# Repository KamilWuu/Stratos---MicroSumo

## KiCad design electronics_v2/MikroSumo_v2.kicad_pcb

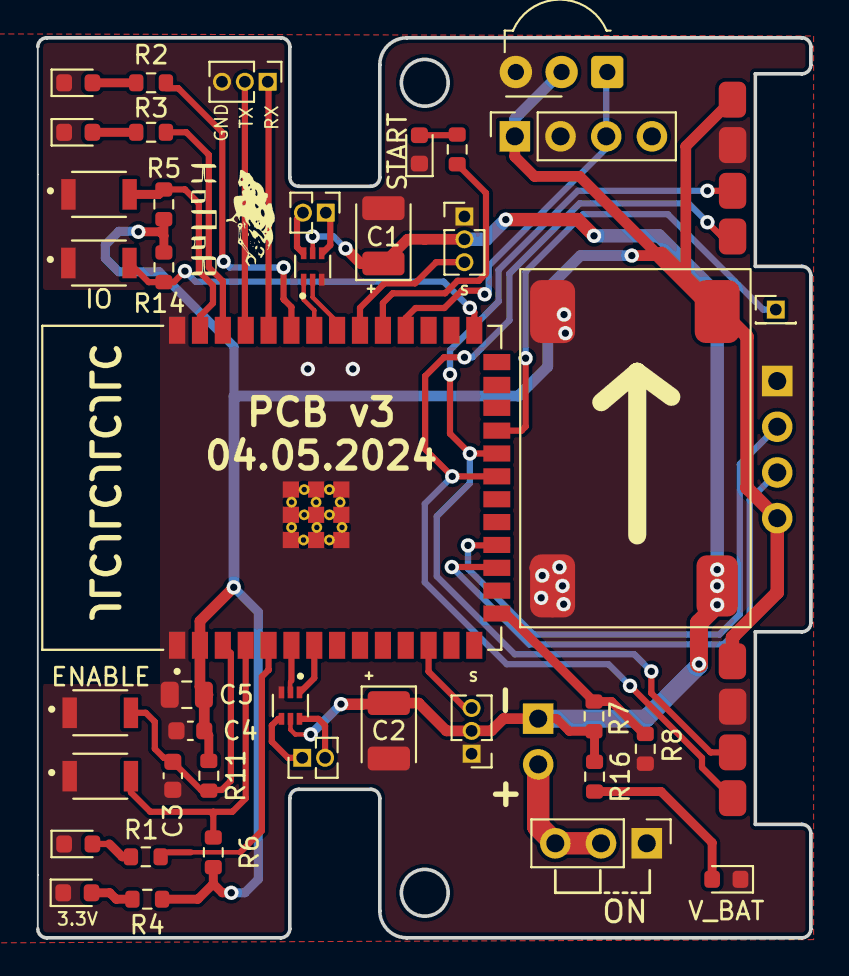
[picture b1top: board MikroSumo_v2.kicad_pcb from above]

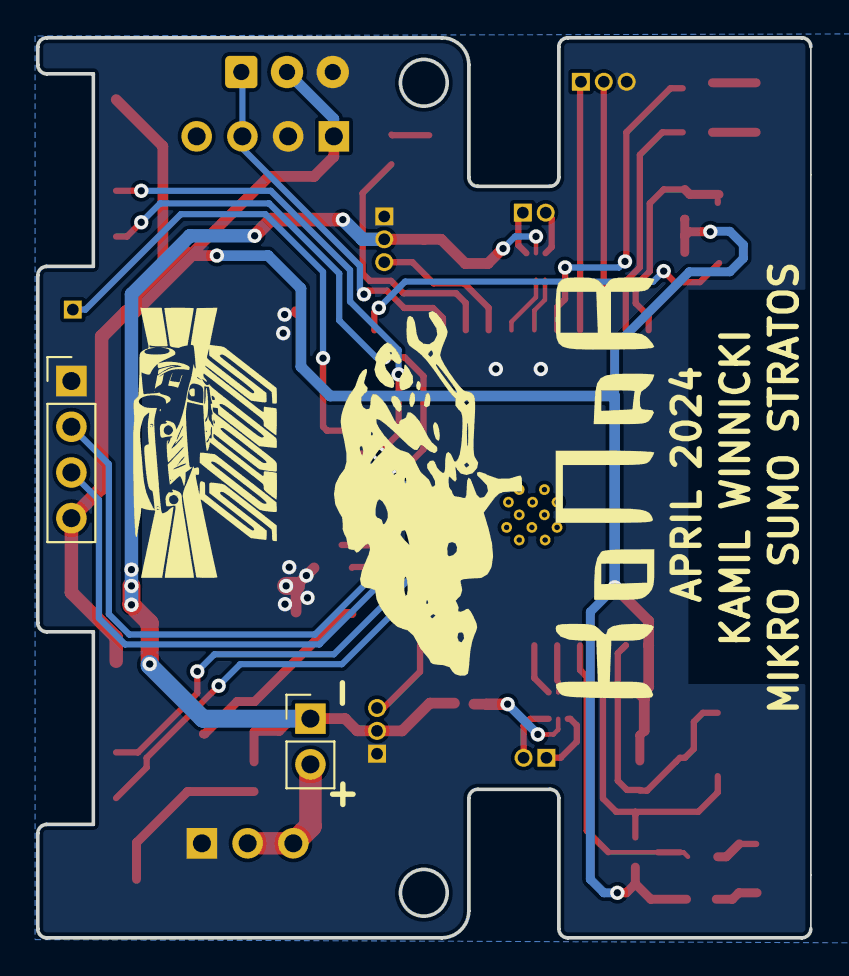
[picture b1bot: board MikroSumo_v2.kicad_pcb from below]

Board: 2 copper layers, 42.9 x 50.0 mm, 44 parts (2 on the bottom side), 37 nets.

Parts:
3.3V: LED; LED_0603_1608Metric
C1, C2: C_Polarized; CP_EIA-3528-21_Kemet-B
C3, C4: 0.1uF; C_0603_1608Metric
C5: 22uF; C_0805_2012Metric
ENABLE: B3U-1000P; SW_B3U-1000P
IO: B3U-1000P; SW_B3U-1000P
J1: Conn_01x04_Female; PinHeader_1x04_P2.54mm_Vertical
J3, J4: Conn_01x02_Male; PinHeader_1x02_P1.27mm_Vertical
J5: Conn_01x01_Male; PinHeader_1x01_P1.27mm_Vertical
J6: Conn_01x03_Male; PinHeader_1x03_P1.27mm_Vertical
J8: Conn_01x04_Female; PinSocket_1x04_P2.54mm_Vertical
J9: Conn_01x03_Pin; PinHeader_1x03_P2.54mm_Vertical
LED1, LED2, LED3: LED; LED_0603_1608Metric
R1, R2, R3, R4, R15: 1K; R_0603_1608Metric
R5, R6, R7, R8, R11, R14: 10K; R_0603_1608Metric
R16: 2K; R_0603_1608Metric
S1, S2: B3U-1000P; SW_B3U-1000P
START: LED; LED_0603_1608Metric
SV1, SV2: Conn_01x03_Male; PinHeader_1x03_P1.27mm_Vertical
U1: MH-MINI-360
U2, U3: DRV8210DRLR; SOT50P160X60-6N
U6, U7: TOFVL53L0X
U8: ESP32-S3-WROOM-1-N8R8; XCVR_ESP32S3WROOM1N8R8
U9: TSOP323xx; Vishay_MOLD-3Pin
V_BAT: LED; LED_0603_1608Metric
batt1: Conn_01x02_Male; PinHeader_1x02_P2.54mm_Vertical

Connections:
+3.3V: C4.2, C5.2, J1.4, J8.1, R4.1, R5.1, R6.1, R11.2, R14.2, U1.4 (OUT+), U6.1 (VIN), U7.1 (VIN), U8.2 (3V3), U9.2 (Vs)
B1: R6.2, S2.2, U8.4 (IO4)
B2: R5.2, S1.2, U8.39 (IO1)
EN: C3.1, ENABLE.2, R11.1, U8.3 (EN)
GND: 3.3V.1 (K), C1.2, C2.2, C3.2, C4.1, C5.1, ENABLE.1, IO.1, J1.1, J6.3, J8.2, J9.1, LED1.1 (K), LED2.1 (K), LED3.1 (K), R8.1, S1.1, S2.1, START.1 (K), SV1.1, SV2.1, U1.1 (IN-), U1.3 (OUT-), U2.3 (GND), U3.3 (GND), U6.2 (GND), U7.2 (GND), U8.1 (GND), U8.40 (GND), U8.41_1 (GND), U8.41_2 (GND), U8.41_3 (GND), U8.41_4 (GND), U8.41_5 (GND), U8.41_6 (GND), U8.41_7 (GND), U8.41_8 (GND), U8.41_9 (GND), U9.3 (GND), V_BAT.1 (K)
IN_1: J1.3, U8.17 (IO9)
IN_2: J1.2, U8.18 (IO10)
IO0: IO.2, R14.1, U8.27 (IO0)
LED1: R1.1, U8.5 (IO5)
LED2: R3.1, U8.38 (IO2)
LED3: R2.1, U8.35 (IO42)
MIN1_1: U2.1 (IN1), U8.7 (IO7)
MIN1_2: U3.1 (IN1), U8.34 (IO41)
MIN2_1: U2.2 (IN2), U8.6 (IO6)
MIN2_2: U3.2 (IN2), U8.33 (IO40)
unnamed: 3.3V.2 (A), R4.2
unnamed: J3.1, U2.4 (OUT2)
unnamed: J3.2, U2.6 (OUT1)
unnamed: J4.1, U3.4 (OUT2)
unnamed: J4.2, U3.6 (OUT1)
unnamed: J9.2, J9.3, batt1.2
unnamed: LED1.2 (A), R1.2
unnamed: LED2.2 (A), R2.2
unnamed: LED3.2 (A), R3.2
unnamed: R15.2, START.2 (A)
unnamed: R16.2, V_BAT.2 (A)
RX: J6.1, U8.36 (RXD0)
SCL: U6.3 (SCL), U7.3 (SCL), U8.22 (IO14)
SDA: U6.4 (SDA), U7.4 (SDA), U8.21 (IO13)
SERVO1: SV1.3, U8.12 (IO8)
SERVO2: SV2.3, U8.32 (IO39)
STARTER: J8.3, U8.30 (IO37), U9.1 (OUT)
STARTER_LED: R15.1, U8.31 (IO38)
TX: J6.2, U8.37 (TXD0)
VCC: C1.1, C2.1, R7.2, R16.1, SV1.2, SV2.2, U1.2 (IN+), U2.5 (VM), U3.5 (VM), batt1.1
V_BAT: R7.1, R8.2, U8.15 (IO3)
XSHUT: J5.1, U8.23 (IO21)

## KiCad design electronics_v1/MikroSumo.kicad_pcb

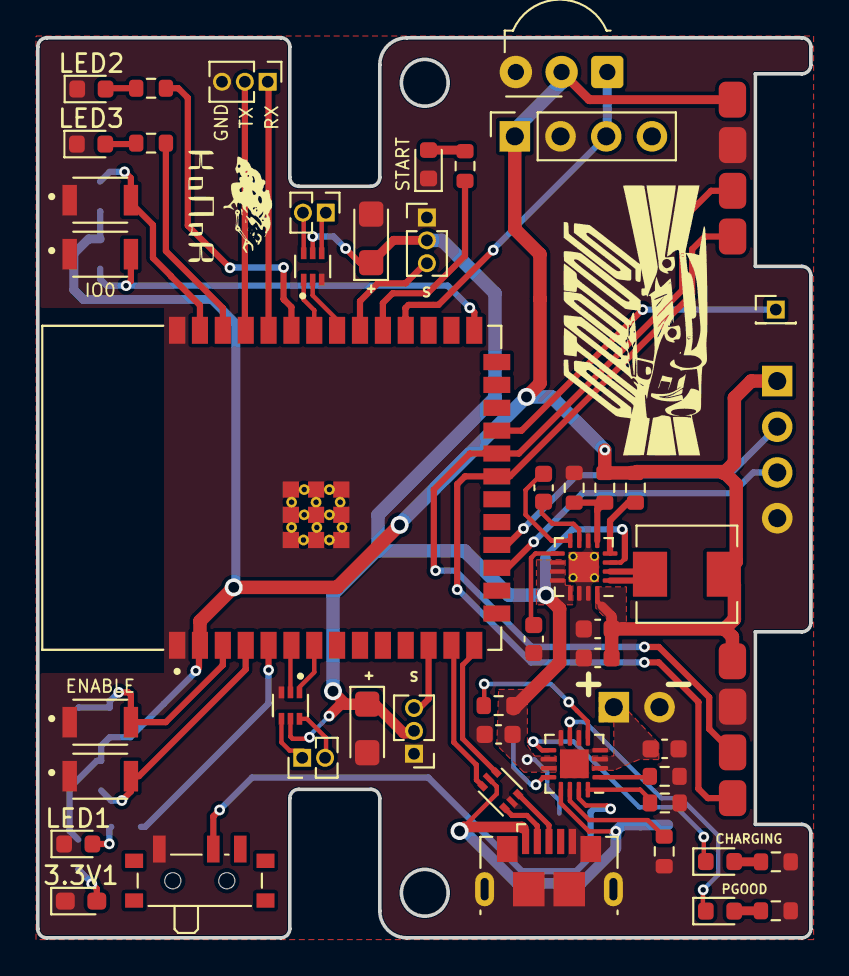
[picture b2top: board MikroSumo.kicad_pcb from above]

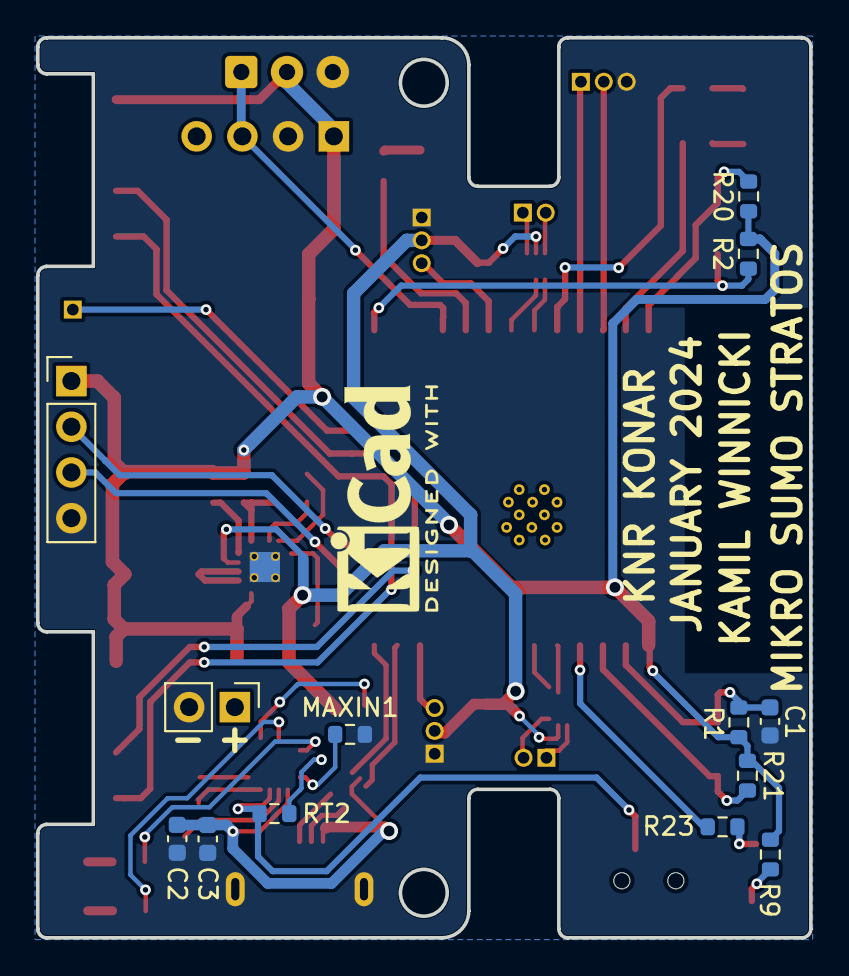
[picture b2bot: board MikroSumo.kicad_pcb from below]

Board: 4 copper layers, 42.9 x 50.0 mm, 63 parts (13 on the bottom side), 56 nets.

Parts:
3.3V1: LED; LED_0603_1608Metric_Pad1.05x0.95mm_HandSolder
C1: 0.1uF; C_0603_1608Metric
C2, C3: 47u; C_0603_1608Metric
C4, C5, C8, C9: 22u; C_0603_1608Metric
C6, C7: 10n; C_0603_1608Metric
C10, C11: C_Polarized; CP_EIA-3216-18_Kemet-A
CHARGING: LED; LED_0603_1608Metric
ENABLE: B3U-1000P; SW_B3U-1000P
IO0: B3U-1000P; SW_B3U-1000P
ISET1: 1.8K; R_0603_1608Metric
J1: USB_B_Micro; USB_Micro-B_GCT_USB3076-30-A
J2: Conn_01x03_Male; PinHeader_1x03_P1.27mm_Vertical
J3: Conn_01x01_Male; PinHeader_1x01_P1.27mm_Vertical
J4: Conn_01x04_Female; PinSocket_1x04_P2.54mm_Vertical
J5, J8: Conn_01x02_Male; PinHeader_1x02_P1.27mm_Vertical
J6: Conn_01x04_Female; PinHeader_1x04_P2.54mm_Vertical
L1: 1u; L_Sunlord_MWSA0518_5.4x5.2mm
LED1, LED2, LED3: LED; LED_0603_1608Metric
MAXIN1: 1.1K; R_0603_1608Metric
PGOOD: LED; LED_0603_1608Metric
R1, R2, R3, R20, R21: 10K; R_0603_1608Metric
R4, R5, R9, R22, R23, R24, R25: 1K; R_0603_1608Metric
R6, R7: 470K; R_0603_1608Metric
R8: 150K; R_0603_1608Metric
RT1, RT2: 10K; R_0603_1608Metric
S3, S4: B3U-1000P; SW_B3U-1000P
START: LED; LED_0603_1608Metric
SV1, SV2: Conn_01x03_Male; PinHeader_1x03_P1.27mm_Vertical
SW1: SW_DIP_x01; SW_SPDT_PCM12
TMR1: 45.4K; R_0603_1608Metric
U1: BQ24075RGT; VQFN-16-1EP_3x3mm_P0.5mm_EP1.6x1.6mm
U2: ESP32-S3-WROOM-1-N8R8; XCVR_ESP32S3WROOM1N8R8
U3: TLV62095RGTx; VQFN-16-1EP_3x3mm_P0.5mm_EP1.68x1.68mm_ThermalVias
U4, U5: DRV8210DRLR; SOT50P160X60-6N
U6: USBLC6-2P6; SOT-666
U9, U10: TOFVL53L0X
U11: TSOP323xx; Vishay_MOLD-3Pin
batt1: Conn_01x02_Male; PinHeader_1x02_P2.54mm_Vertical

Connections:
+3.3V: C8.1, C9.1, J4.1, J6.1, L1.2, R1.2, R2.2, R6.1, R7.1, R9.1, R20.1, R21.1, U2.2 (3V3), U3.16 (VOS), U9.1 (VIN), U10.1 (VIN), U11.2 (Vs)
+5V: C2.1, C3.1, J1.1 (VBUS), U1.13 (IN), U6.5 (VBUS)
+BATT: C5.1, U1.2 (BAT), U1.3 (BAT), batt1.1
AGND: 3.3V1.1 (K), C1.2, C2.2, C3.2, C4.2, C5.2, C6.2, C8.2, C9.2, C10.2, C11.2, ENABLE.1, IO0.1, ISET1.2, J1.5 (GND), J1.6 (Shield), J2.3, J4.2, J6.4, LED1.1 (K), LED2.1 (K), LED3.1 (K), MAXIN1.2, R4.2, R5.2, R8.2, RT1.2, S3.1, S4.1, START.1 (K), SV1.1, SV2.1, SW1.1, TMR1.2, U1.4 (~CE), U1.6 (EN1), U1.8 (VSS), U1.17 (VSS), U2.1 (GND), U2.40 (GND), U2.41_1 (GND), U2.41_2 (GND), U2.41_3 (GND), U2.41_4 (GND), U2.41_5 (GND), U2.41_6 (GND), U2.41_7 (GND), U2.41_8 (GND), U2.41_9 (GND), U3.6 (AGND), U3.14 (PGND), U3.15 (PGND), U3.17 (AGND), U4.3 (GND), U5.3 (GND), U6.2 (GND), U9.2 (GND), U10.2 (GND), U11.3 (GND), batt1.2
B1: R21.2, S4.2, U2.4 (IO4)
B2: R20.2, S3.2, U2.39 (IO1)
EN: C1.1, ENABLE.2, R1.1, U2.3 (EN)
IN_1: J6.3, U2.17 (IO9)
IN_2: J6.2, U2.18 (IO10)
IO0: IO0.2, R2.1, U2.27 (IO0)
LED1: R23.1, U2.5 (IO5)
LED2: R25.1, U2.38 (IO2)
LED3: R24.1, U2.35 (IO42)
MIN1_1: U2.7 (IO7), U4.1 (IN1)
MIN1_2: U2.34 (IO41), U5.1 (IN1)
MIN2_1: U2.6 (IO6), U4.2 (IN2)
MIN2_2: U2.33 (IO40), U5.2 (IN2)
unnamed: 3.3V1.2 (A), R9.2
unnamed: C6.1, U3.9 (SS)
unnamed: C7.1, U3.7 (CP)
unnamed: C7.2, U3.8 (CN)
unnamed: CHARGING.1 (K), U1.9 (~CHG)
unnamed: CHARGING.2 (A), R4.1
unnamed: ISET1.1, U1.16 (ISET)
unnamed: J5.1, U4.4 (OUT2)
unnamed: J5.2, U4.6 (OUT1)
unnamed: J8.1, U5.4 (OUT2)
unnamed: J8.2, U5.6 (OUT1)
unnamed: L1.1, U3.1 (SW), U3.2 (SW)
unnamed: LED1.2 (A), R23.2
unnamed: LED2.2 (A), R24.2
unnamed: LED3.2 (A), R25.2
unnamed: MAXIN1.1, U1.12 (ILIM)
unnamed: PGOOD.1 (K), U1.7 (~PGOOD)
unnamed: PGOOD.2 (A), R5.1
unnamed: R3.1, U1.5 (EN2)
unnamed: R6.2, U3.4 (PG)
unnamed: R7.2, R8.1, U3.5 (FB)
unnamed: R22.2, START.2 (A)
unnamed: RT1.1, U1.1 (TS)
unnamed: RT2.2, SW1.2, U1.15 (SYSOFF)
unnamed: TMR1.1, U1.14 (TMR)
RX: J2.1, U2.36 (RXD0)
SCL: U2.22 (IO14), U9.3 (SCL), U10.3 (SCL)
SDA: U2.21 (IO13), U9.4 (SDA), U10.4 (SDA)
SERVO1: SV2.3, U2.12 (IO8)
SERVO2: SV1.3, U2.32 (IO39)
STARTER: J4.3, U2.30 (IO37), U11.1 (OUT)
STARTER_LED: R22.1, U2.31 (IO38)
TX: J2.2, U2.37 (TXD0)
USB+: U2.14 (IO20), U6.4 (I/O2)
USB-: U2.13 (IO19), U6.6 (I/O1)
USBN: J1.2 (D-), U6.1 (I/O1)
USBP: J1.3 (D+), U6.3 (I/O2)
VCC: C4.1, C10.1, C11.1, R3.2, RT2.1, SV1.2, SV2.2, U1.10 (OUT), U1.11 (OUT), U3.3 (DEF), U3.10 (AVIN), U3.11 (PVIN), U3.12 (PVIN), U3.13 (EN), U4.5 (VM), U5.5 (VM)
XSHUT: J3.1, U2.23 (IO21)

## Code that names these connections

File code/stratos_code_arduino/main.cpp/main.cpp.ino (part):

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#define LED_1 5
#define LED_2 2
#define LED_3 42
#define STARTER_LED 38

#define XSHUT 21
#define RIGHT_XSHUT 8

// ANALOG_OUTPUTS
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// DIGITAL_INPUTS
#define BUTTON_LEFT 1
#define BUTTON_RIGHT 4
#define STARTER_PIN 37

// ANALOG INPUTS
#define LEFT_GROUND_SENSOR 10
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  pinMode(LED_1, OUTPUT);
  pinMode(LED_2, OUTPUT);
  pinMode(LED_3, OUTPUT);
  pinMode(STARTER_LED, OUTPUT);

  // Konfiguracja pinów pwm
  pinMode(L_MOT_FORW, OUTPUT);
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  // Konfiguracja wejść cyfrowych
  pinMode(BUTTON_LEFT, INPUT);
  pinMode(BUTTON_RIGHT, INPUT);
  pinMode(STARTER_PIN, INPUT);

  // Konfiguracja wejść analogowych (ESP32 używa ADC)
  pinMode(LEFT_GROUND_SENSOR, INPUT);
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void DistanceSensors::initDistanceSensors()
{

  pinMode(XSHUT, OUTPUT);
  pinMode(RIGHT_XSHUT, OUTPUT);
  digitalWrite(XSHUT, LOW);
  digitalWrite(RIGHT_XSHUT, LOW);
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  void readSensors(); // Funkcja do odczytu czujników
  bool readStarter()
  {
    starter_state = digitalRead(STARTER_PIN);
    return starter_state;
  };
  void checkButtonClicks();
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
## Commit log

2024-05-01 utworzono repozytorium
2024-05-02 poprawki w 3 wersji
2024-05-04 przygotowanie pcb do produkcji
2025-03-17 mechanics v2 started
2025-03-27 pierwszy prototyp mechaniki v2
2025-03-27 zrobiono kolka
2025-03-31 prawie dzialajacy kod
2025-03-31 mechanikav2.2
2025-04-01 mechanikav2.2_dalej
2025-04-02 kod prawie skonczony
2025-04-02 wstepnei dodane unikanie lini
2025-04-03 kod wstepny chyba szukanie przeciwnika, reakcja na linie
2025-04-04 program dziala, trzeba wyregulowac czasy
